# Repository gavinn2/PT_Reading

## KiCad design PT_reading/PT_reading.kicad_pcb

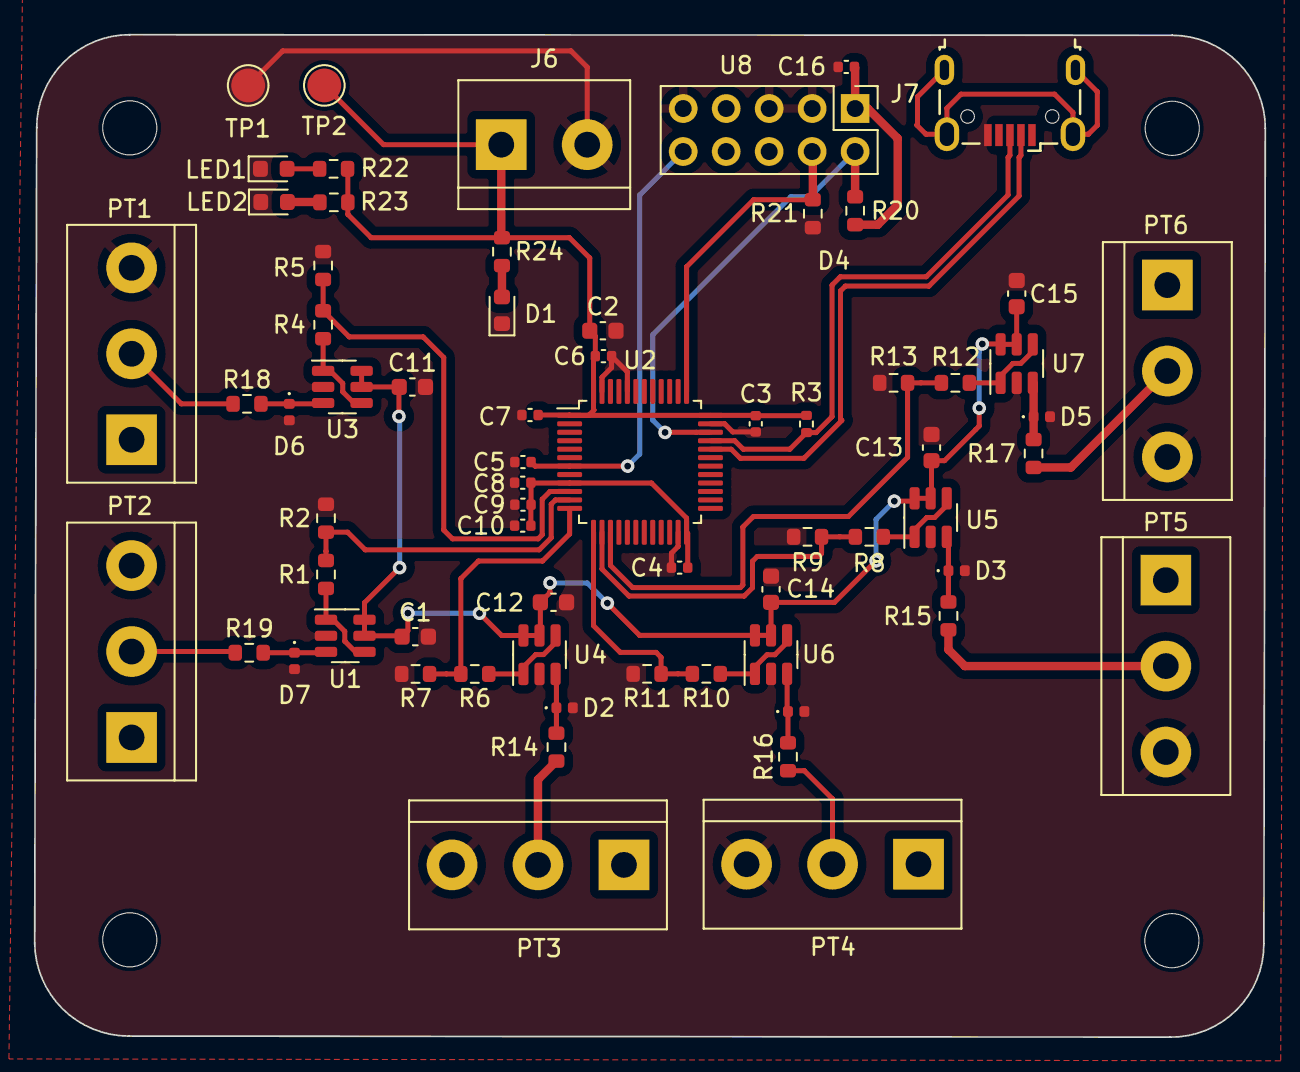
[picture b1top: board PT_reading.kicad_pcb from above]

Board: 4 copper layers, 72.7 x 59.3 mm, 71 parts (0 on the bottom side), 36 nets.

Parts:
C1, C11, C12, C13, C14, C15: 100nF; C_0603_1608Metric
C2: 10uF; C_0603_1608Metric
C3, C4, C5, C6, C7, C9: 100nF; C_0402_1005Metric
C8: 10nF; C_0402_1005Metric
C10: 1uF; C_0402_1005Metric
C16: 500nF; C_0402_1005Metric
D1: LED; LED_0603_1608Metric
D2, D3, D4, D5, D7: 5.0V; D_0402_1005Metric
D6: 5V; D_0402_1005Metric
H1, H2, H3, H4: MountingHole; MountingHole_3.2mm_M3
J6: Conn_01x02_Pin; TerminalBlock_bornier-2_P5.08mm
J7: USB_B_Micro; USB_Micro-B_Wuerth_629105150521
LED1, LED2: LED; LED_0603_1608Metric
PT1, PT2, PT3, PT4, PT5, PT6: Pressure Transducer 0; TerminalBlock_bornier-3_P5.08mm
R1, R2, R4, R5, R6, R7, R8, R9, R10, R11, R12, R13: 4.7K; R_0603_1608Metric
R3: 1k5; R_0402_1005Metric
R14, R15, R16, R17, R18, R19: 1K; R_0603_1608Metric
R20, R21: 100k; R_0603_1608Metric
R22, R23, R24: 1k5; R_0603_1608Metric
TP1, TP2: TestPoint; TestPoint_Pad_D2.0mm
U1, U3, U4, U5, U6, U7: OPA357; SOT-23-6
U2: LQFP-48_7x7mm_P0.5mm
U8: PinHeader_2x05_P2.54mm_Vertical

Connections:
+3.3V: C2.1, C3.1, C4.1, C6.1, C7.1, C8.1, C9.1, C10.1, C16.2, J6.1, R3.1, R20.1, R22.2, R23.2, R24.1, TP2.1, U2.1 (VBAT), U2.9 (VDDA), U2.24 (VDD), U2.36 (VDD), U2.48 (VDD), U8.1 (VCC)
+5V: C1.1, C11.1, C12.1, C13.1, C14.1, C15.1, U1.5 (EN), U1.6 (V+), U3.5 (EN), U3.6 (V+), U4.5 (EN), U4.6 (V+), U5.5 (EN), U5.6 (V+), U6.5 (EN), U6.6 (V+), U7.5 (EN), U7.6 (V+)
+24V: PT1.1, PT2.1, PT3.1, PT4.1, PT5.1, PT6.1
GND: C1.2, C2.2, C3.2, C4.2, C5.2, C6.2, C7.2, C8.2, C9.2, C10.2, C11.2, C12.2, C13.2, C14.2, C15.2, C16.1, D1.1 (K), D2.2 (A), D3.2 (A), D4.2 (A), D5.2 (A), D6.2 (A), D7.2 (A), J6.2, J7.5 (GND), LED1.1 (K), LED2.1 (K), PT1.3, PT2.3, PT3.3, PT4.3, PT5.3, PT6.3, R2.2, R5.2, R7.2, R9.2, R11.2, R13.2, R21.1, TP1.1, U1.2 (V-), U2.8 (VSSA), U2.23 (VSS), U2.35 (VSS), U2.44 (BOOT0), U2.47 (VSS), U3.2 (V-), U4.2 (V-), U5.2 (V-), U6.2 (V-), U7.2 (V-), U8.3 (GND), U8.5 (GND), U8.9 (GND_detect)
unnamed: D1.2 (A), R24.2
unnamed: D2.1 (K), R14.2, U4.3 (+)
unnamed: D3.1 (K), R15.2, U5.3 (+)
unnamed: D4.1 (K), R16.2, U6.3 (+)
unnamed: D5.1 (K), R17.2, U7.3 (+)
unnamed: D6.1 (K), R18.2, U3.3 (+)
unnamed: D7.1 (K), R19.2, U1.3 (+)
unnamed: J7.2 (D-), U2.32 (PA11)
unnamed: LED1.2 (A), R22.1
unnamed: LED2.2 (A), R23.1
unnamed: PT1.2, R18.1
unnamed: PT2.2, R19.1
unnamed: PT3.2, R14.1
unnamed: PT4.2, R16.1
unnamed: PT5.2, R15.1
unnamed: PT6.2, R17.1
unnamed: R1.1, U1.1, U1.4 (-)
unnamed: R4.1, U3.1, U3.4 (-)
unnamed: R6.1, U4.1, U4.4 (-)
unnamed: R8.1, U5.1, U5.4 (-)
unnamed: R10.1, U6.1, U6.4 (-)
unnamed: R12.1, U7.1, U7.4 (-)
PT0: R4.2, R5.1, U2.10 (PA0)
PT1: R1.2, R2.1, U2.11 (PA1)
PT2: R6.2, R7.1, U2.12 (PA2)
PT3: R10.2, R11.1, U2.13 (PA3)
PT4: R8.2, R9.1, U2.14 (PA4)
PT5: R12.2, R13.1, U2.15 (PA5)
Pull_Up: J7.3 (D+), R3.2, U2.33 (PA12)
SWCLK: R21.2, U2.37 (PA14), U8.4 (SWCLK/TCK)
SWDIO: R20.2, U2.34 (PA13), U8.2 (SWDIO/TMS)
nRST: C5.1, U2.7 (~RST), U8.10 (nRST)

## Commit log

2023-12-04 Add PT files
